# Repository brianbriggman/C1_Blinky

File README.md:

# C1_Blinky

The 'firmware' directory contains the firmware that gets flashed to the ATtiny85.  It can be re-built and re-flashed with a 'make clean' and 'make program'.

The 'commandline' directory contains the 'set-led' executable that sends R G B values to the 'C1_Blinky' connected to the USB port.  It can be re-built with a 'make clean' and 'make'.

Once compiled, you can execute 'set-led' using the format:  
  
	sudo ./set-led 255 0 0  
  
Where the 3 values following the 'set-led' command are the R(ed), G(reen), and B(lue) values respectively.  (The command above sets the C1 Blinky to full intensity red.)

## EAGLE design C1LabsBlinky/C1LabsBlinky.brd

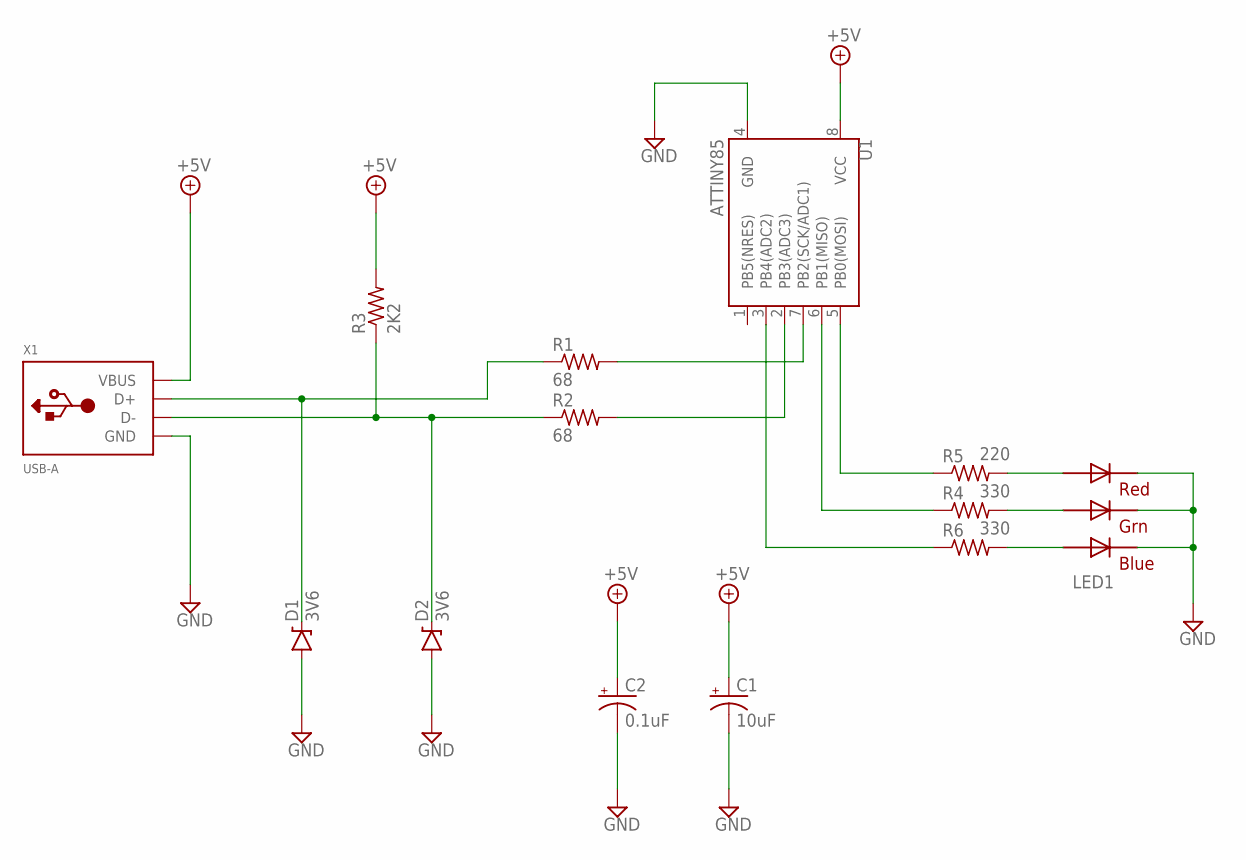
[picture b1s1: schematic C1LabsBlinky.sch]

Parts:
C1: 10uF; CPOL-RADIAL-10UF-25V
C2: 0.1uF; TT2D5
D1, D2: 3V6; DIODE-ZENER
LED1: RGBLED5050
R1, R2: 68; 0207/10
R3: 2K2; 0207/10
R4, R6: 330; 0207/10
R5: 220; 0207/10
U1: ATTINY85; DIP08
X1: USB-A; MOLEX_480371000

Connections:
+5V: C1.1 (+), C2.+, R3.2, U1.8 (VCC), X1.1 (VBUS)
GND: C1.2 (-), C2.-, D1.P$2 (A), D2.P$2 (A), LED1.4 (BLUE_C), LED1.5 (RED_C), LED1.6 (GREEN_C), U1.4 (GND), X1.4 (GND)
unnamed: D1.P$1 (C), R1.1, X1.3 (D+)
unnamed: D2.P$1 (C), R2.1, R3.1, X1.2 (D-)
unnamed: LED1.2 (RED_A), R5.2
unnamed: LED1.1 (GREEN_A), R4.2
unnamed: LED1.3 (BLUE_A), R6.2
unnamed: R5.1, U1.5 (PB0(MOSI))
unnamed: R1.2, U1.7 (PB2(SCK/ADC1))
unnamed: R4.1, U1.6 (PB1(MISO))
unnamed: R2.2, U1.2 (PB3(ADC3))
unnamed: R6.1, U1.3 (PB4(ADC2))

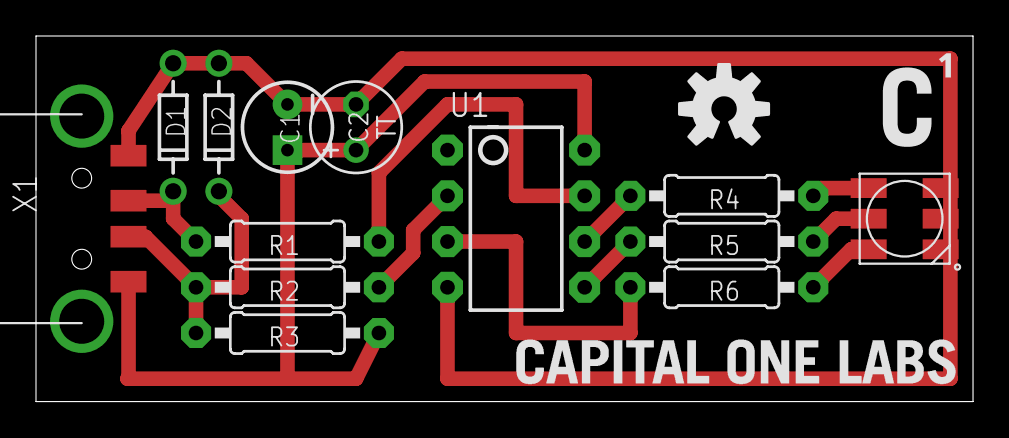
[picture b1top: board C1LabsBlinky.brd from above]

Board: 2 copper layers, 52.1 x 20.3 mm, 16 parts (0 on the bottom side), 12 nets.

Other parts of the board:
U$1: C1_LABS_NAME_POS
U$2: OSHW-LOGO-M
U$3: C1_LABS_LOGO_S

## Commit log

2015-05-20 Added README.md
2015-05-20 Added C1LabsBlinky directory containing Eagle PCB files and Gerber files for PCB Manufacturing
2015-05-20 Create gh-pages branch via GitHub
2015-05-20 Update for capitalization

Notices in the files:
parts and their libraries:
SparkFun-DiscreteSemi: Licensing: Creative Commons ShareAlike 4.0 International - https://creativecommons.org/licenses/by-sa/4.0
